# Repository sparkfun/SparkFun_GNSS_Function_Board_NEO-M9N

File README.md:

SparkFun MicroMod GNSS Function Board - NEO-M9N
========================================

[*SparkFun MicroMod GNSS Function Board - NEO-M9N (GPS-18378)*](https://www.sparkfun.com/products/18378)

The SparkFun NEO-M9N GNSS Function Board is a high quality, geospatial board with equally impressive configuration options. The NEO-M9N module that is populated on this board is a 92-channel u-blox M9 engine GNSS receiver, meaning it can receive signals from the GPS, GLONASS, Galileo, and BeiDou constellations with ~1.5 meter accuracy. This Function Board supports concurrent reception of four GNSS. This maximizes position accuracy in challenging conditions, increasing precision and decreases lock time; and thanks to the on-board rechargeable battery, you'll have backup power enabling the GPS to get a hot lock within seconds!

Utilizing our handy M.2 MicroMod connector, no soldering is required to connect it to your system. Simply match up the key on your processor and function board's beveled edge connector to their respective key on the M.2 connector, then secure them to the Main Board with screws. Once connected, you'll have the option of choosing either the UART, SPI, or I<sup>2</sup>C (u-blox calls this Display Data Channel) port to communicate with the NEO-M9N.

The NEO-M9N module detects jamming and spoofing events and can reports them to the host, so that the system can react to such events. A SAW (Surface Acoustic Wave) filter combined with an LNA (Low Noise Amplifier) in the RF path is integrated into the NEO-M9N module which allows normal operation even under strong RF interferences.

U-blox based GPS products are configurable using the popular, but dense, Windows program called u-center. Plenty of different functions can be configured on the NEO-M9N: baud rates, update rates, geofencing, spoofing detection, external interrupts, SBAS/D-GPS, etc. All of this can be done within the [SparkFun Arduino Library](https://github.com/sparkfun/SparkFun_u-blox_GNSS_Arduino_Library) via the I<sup>2</sup>C bus!

The SparkFun GNSS Function Board - NEO-M9N includes a USB type C connector when configuring the module with u-center. Power is provided through the Function Board's edge pins and regulated down through the 3.3V voltage regulator. Two status LEDs are also included for 3V3 and PPS, which can be disabled by cutting the jumpers on the back of the board. A 1x3 header is populated on the board and includes a 2-pin selectable jumper when selecting the communication protocol between SPI or Serial/I<sup>2</sup>C. For advanced users, there are jumpers to disable the write protection for the EEPROM (WP), disconnecting the pull-up resistors (I2C), and placing the module in safe boot mode (SAFEBOOT). A U.FL connector is provided to connect a GNSS antenna of your choice to the module.  The board is equipped with an on-board rechargeable battery that provides power to the RTC on the NEO-M9N.  This reduces the time-to-first fix from a cold start (~24s) to a hot start (~2s). The battery will maintain RTC and GNSS orbit data without being connected to power for plenty of time. 

Repository Contents
-------------------

* **/Hardware** - Eagle design files (.brd, .sch)
* **/Production** - Production panel files (.brd)

Documentation
--------------

* **[Installing an Arduino Library Guide](https://learn.sparkfun.com/tutorials/installing-an-arduino-library/all)** - Basic information on how to install an Arduino library.
* **[Library](https://github.com/sparkfun/SparkFun_u-blox_GNSS_Arduino_Library)** - Arduino Library the SparkFun MicroMod GNSS Function Board - NEO-M9N.
* **[Hookup Guide](https://learn.sparkfun.com/tutorials/1999)** - Basic hookup guide for the SparkFun MicroMod GNSS Function Board - NEO-M9N.

Product Versions
----------------

* [GPS-18378](https://www.sparkfun.com/products/18378) - Initial release

Version History
---------------

* v1.2 - Initial Release

License Information
-------------------

This product is _**open source**_! 

Please review the LICENSE.md file for license information. 

If you have any questions or concerns on licensing, please contact technical support on our [SparkFun forums](https://forum.sparkfun.com/viewforum.php?f=152).

Distributed as-is; no warranty is given.

- Your friends at SparkFun.

_<COLLABORATION CREDIT>_

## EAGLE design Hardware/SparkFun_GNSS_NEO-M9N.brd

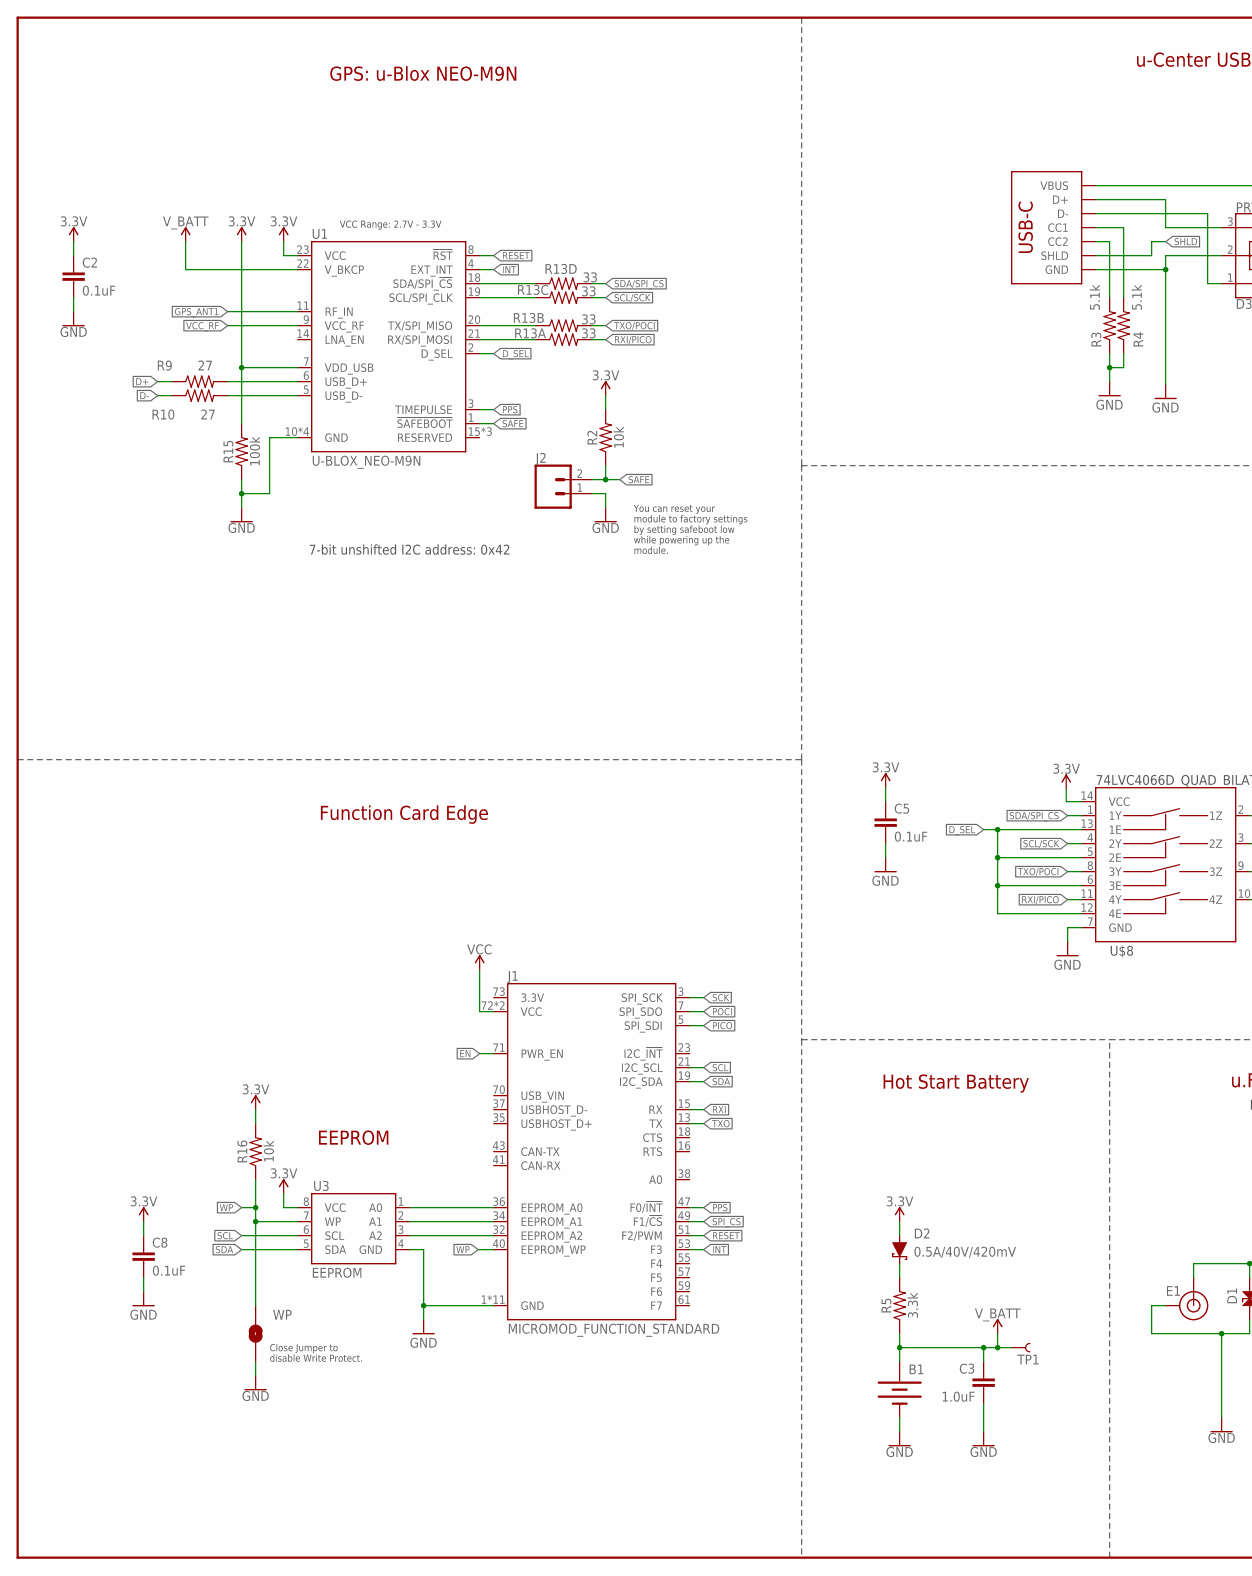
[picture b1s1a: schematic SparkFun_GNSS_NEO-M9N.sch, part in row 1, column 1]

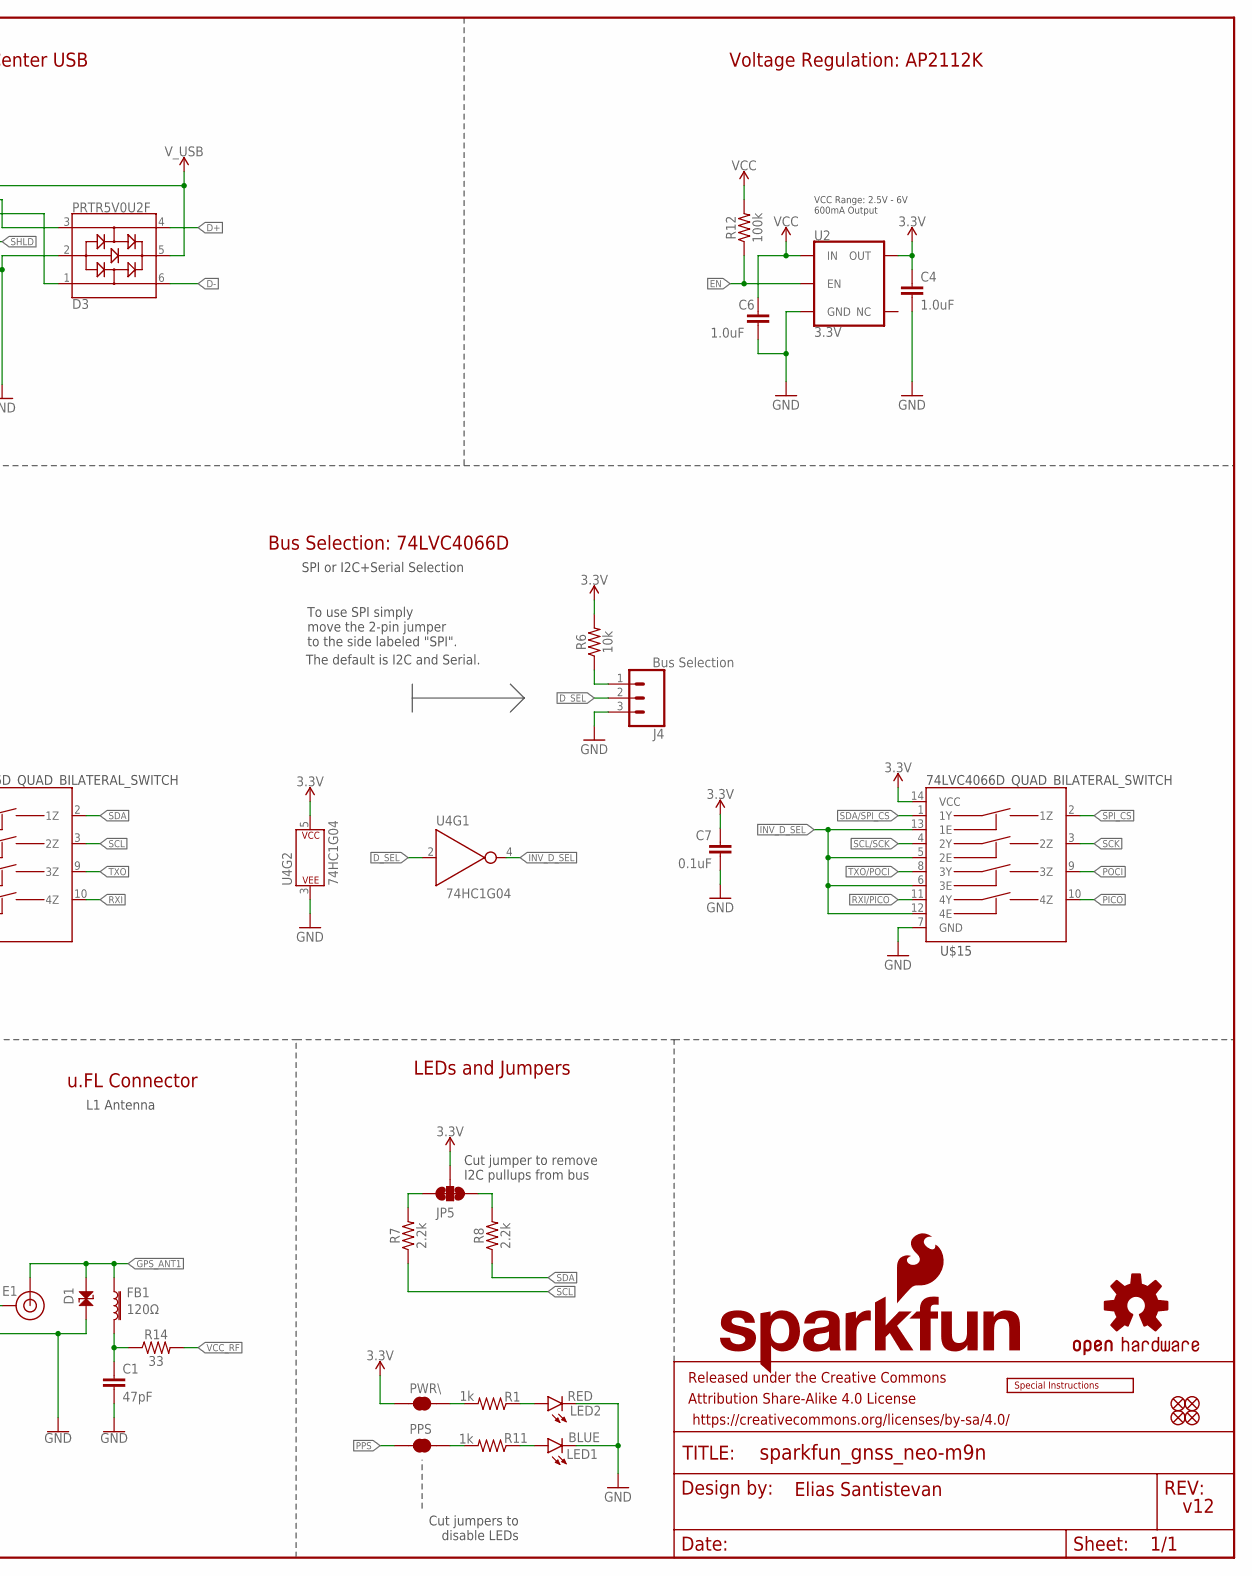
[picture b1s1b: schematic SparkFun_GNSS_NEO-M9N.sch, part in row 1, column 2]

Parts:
B1: 6.8MM_COIN_CELL; MS421R_IV03E
C1: 47pF; 0402
C2: 0.1uF; 0402-TIGHT
C3, C4, C6: 1.0uF; 0603
C5, C7, C8: 0.1uF; 0603
D1: PESD0402-0402T; 0402-TIGHT
D2: 0.5A/40V/420mV; SOD-323
D3: PRTR5V0U2F; SOT886
E1: U.FL
FB1: 120Ω; 0402
FD1, FD2, FD3, FD4: FIDUCIAL1X2; FIDUCIAL-1X2
FRAME2: FRAME-LEDGER; CREATIVE_COMMONS
J1: MICROMOD_FUNCTION_STANDARD; M.2-CARD-E-22_FUNCTION_STANDARD
J2: CONN_02; 1X02
J3: USB_C_2-LAYER_PADS; USB-C-16P-2LAYER-PADS
J4: Bus Selection; 1X03_LOCK
JP5: JUMPER-SMT_3_2-NC_TRACE_SILK; SMT-JUMPER_3_2-NC_TRACE_SILK
LED1: BLUE; LED-0603
LED2: RED; LED-0603
LOGO1: SPECIAL_INSTRUCTIONS-ORDERING; ORDERING_INSTRUCTIONS
LOGO2: SFE_LOGO_NAME_FLAME.2_INCH; SFE_LOGO_NAME_FLAME_.2
LOGO3: OSHW-LOGOS; OSHW-LOGO-S
PPS: JUMPER-SMT_2_NC_TRACE_SILK; SMT-JUMPER_2_NC_TRACE_SILK
PWR\: JUMPER-SMT_2_NC_TRACE_SILK; SMT-JUMPER_2_NC_TRACE_SILK
R1, R11: 1k; 0603
R2, R6, R16: 10k; 0603
R3, R4: 5.1k; 0603
R5: 3.3k; 0603
R7, R8: 2.2k; 0603
R9, R10: 27; 0603
R12, R15: 100k; 0603
R13: 33; 1206_RA
R14: 33; 0402
TP1: TEST-POINT3X4; PAD.03X.04
U1: U-BLOX_NEO-M9N; NEO-M9N/M8T/M8U/D9S
U2: 3.3V; SOT23-5
U3: EEPROM; SO08
U4: 74HC1G04; SOT353
U$8, U$15: 74LVC4066D_QUAD_BILATERAL_SWITCH; SO14
WP: JUMPER-SMT_2_NO_SILK; SMT-JUMPER_2_NO_SILK

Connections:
3.3V: C2.1, C4.1, C5.1, C7.1, C8.1, D2.A, JP5.2, PWR\.2, R2.2, R6.2, R15.2, R16.2, U1.7 (VDD_USB), U1.23 (VCC), U2.5 (OUT), U3.8 (VCC), U4.5 (P$V+), U$8.14 (VCC), U$15.14 (VCC)
!RESET: J1.51 (F2/PWM), U1.8 (!RST)
!SAFE: J2.2, R2.1, U1.1 (!SAFEBOOT!)
A0: J1.36 (EEPROM_A0), U3.1 (A0)
A1: J1.34 (EEPROM_A1), U3.2 (A1)
A2: J1.32 (EEPROM_A2), U3.3 (A2)
D+: D3.4, R9.1
D-: D3.6, R10.1
D_SEL: J4.2, U1.2 (D_SEL), U4.2 (A), U$8.5 (2E), U$8.6 (3E), U$8.12 (4E), U$8.13 (1E)
EN: J1.71 (PWR_EN), R12.1, U2.3 (EN)
GND: B1.-, C1.2, C2.2, C3.2, C4.2, C5.2, C6.2, C7.2, C8.2, D1.1, D3.2, E1.1 (GND), E1.2 (GND), J1.1 (GND), J1.33 (GND), J1.39 (GND), J1.45 (GND), J1.75 (GND), J1.GND1 (GND), J1.GND2 (GND), J1.GND3 (GND), J1.GND4 (GND), J1.GND5 (GND), J1.GND6 (GND), J2.1, J3.GND, J3.GND2 (GND), J4.3, LED1.C, LED2.C, R3.1, R4.1, R15.1, U1.10 (GND), U1.12 (GND), U1.13 (GND), U1.24 (GND), U2.2 (GND), U3.4 (GND), U4.3 (P$V-), U$8.7 (GND), U$15.7 (GND), WP.1
GPS_ANT1: D1.2, E1.FEED (SIGNAL), FB1.1, U1.11 (RF_IN)
INT: J1.53 (F3), U1.4 (EXT_INT)
INV_D_SEL: U4.4 (Y), U$15.5 (2E), U$15.6 (3E), U$15.12 (4E), U$15.13 (1E)
unnamed: PWR\.1, R1.2
unnamed: LED1.A, R11.1
unnamed: C1.1, FB1.2, R14.1
unnamed: PPS.1, R11.2
unnamed: JP5.1, R8.2
unnamed: D2.C, R5.2
unnamed: J3.A5 (CC1), R4.2
unnamed: JP5.3, R7.2
unnamed: J3.B5 (CC2), R3.2
unnamed: LED2.A, R1.1
unnamed: R9.2, U1.6 (USB_D+)
unnamed: R10.2, U1.5 (USB_D-)
unnamed: J4.1, R6.1
PICO: J1.5 (SPI_SDI), U$15.10 (4Z)
POCI: J1.7 (SPI_SDO), U$15.9 (3Z)
PPS: J1.47 (F0/!INT!), PPS.2, U1.3 (TIMEPULSE)
RXI: J1.15 (RX), U$8.10 (4Z)
RXI/PICO: R13.P8 (2), U$8.11 (4Y), U$15.11 (4Y)
RXLV: R13.P1 (1), U1.21 (RX/SPI_MOSI)
SCK: J1.3 (SPI_SCK), U$15.3 (2Z)
SCL: J1.21 (I2C_SCL), R7.1, U3.6 (SCL), U$8.3 (2Z)
SCL/SCK: R13.P6 (2), U$8.4 (2Y), U$15.4 (2Y)
SCL_LV: R13.P3 (1), U1.19 (SCL/SPI_CLK)
SDA: J1.19 (I2C_SDA), R8.1, U3.5 (SDA), U$8.2 (1Z)
SDA/SPI_!CS!: R13.P5 (2), U$8.1 (1Y), U$15.1 (1Y)
SDA_LV: R13.P4 (1), U1.18 (SDA/SPI_!CS!)
SHLD: J3.SHLD1 (SHLD), J3.SHLD2 (SHLD), J3.SHLD3 (SHLD), J3.SHLD4 (SHLD)
SPI_!CS!: J1.49 (F1/!CS!), U$15.2 (1Z)
TXLV: R13.P2 (1), U1.20 (TX/SPI_MISO)
TXO: J1.13 (TX), U$8.9 (3Z)
TXO/POCI: R13.P7 (2), U$8.8 (3Y), U$15.8 (3Y)
USB_D+: D3.3, J3.A6 (D+), J3.B6 (D+)
USB_D-: D3.1, J3.A7 (D-), J3.B7 (D-)
VCC: C6.1, J1.72 (VCC), J1.74 (VCC), R12.2, U2.1 (IN)
VCC_RF: R14.2, U1.9 (VCC_RF)
V_BATT: B1.+, C3.1, R5.1, TP1.1, U1.22 (V_BKCP)
V_USB: D3.5, J3.VBUS1 (VBUS), J3.VBUS2 (VBUS)
WP: J1.40 (EEPROM_WP), R16.1, U3.7 (WP), WP.2

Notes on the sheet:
v12
7-bit unshifted I2C address: 0x42
Cut jumper to remove I2C pullups from bus
Cut jumpers to disable LEDs
Elias Santistevan
LEDs and Jumpers
Hot Start Battery
GPS: u-Blox NEO-M9N
u.FL Connector
VCC Range: 2.7V - 3.3V
VCC Range: 2.5V - 6V 600mA Output
u-Center USB
Function Card Edge
EEPROM
Voltage Regulation: AP2112K
L1 Antenna
Bus Selection: 74LVC4066D
To use SPI simply move the 2-pin jumper to the side labeled "SPI".
SPI or I2C+Serial Selection
The default is I2C and Serial.
Close Jumper to disable Write Protect.
You can reset your module to factory settings by setting safeboot low while powering up the module.

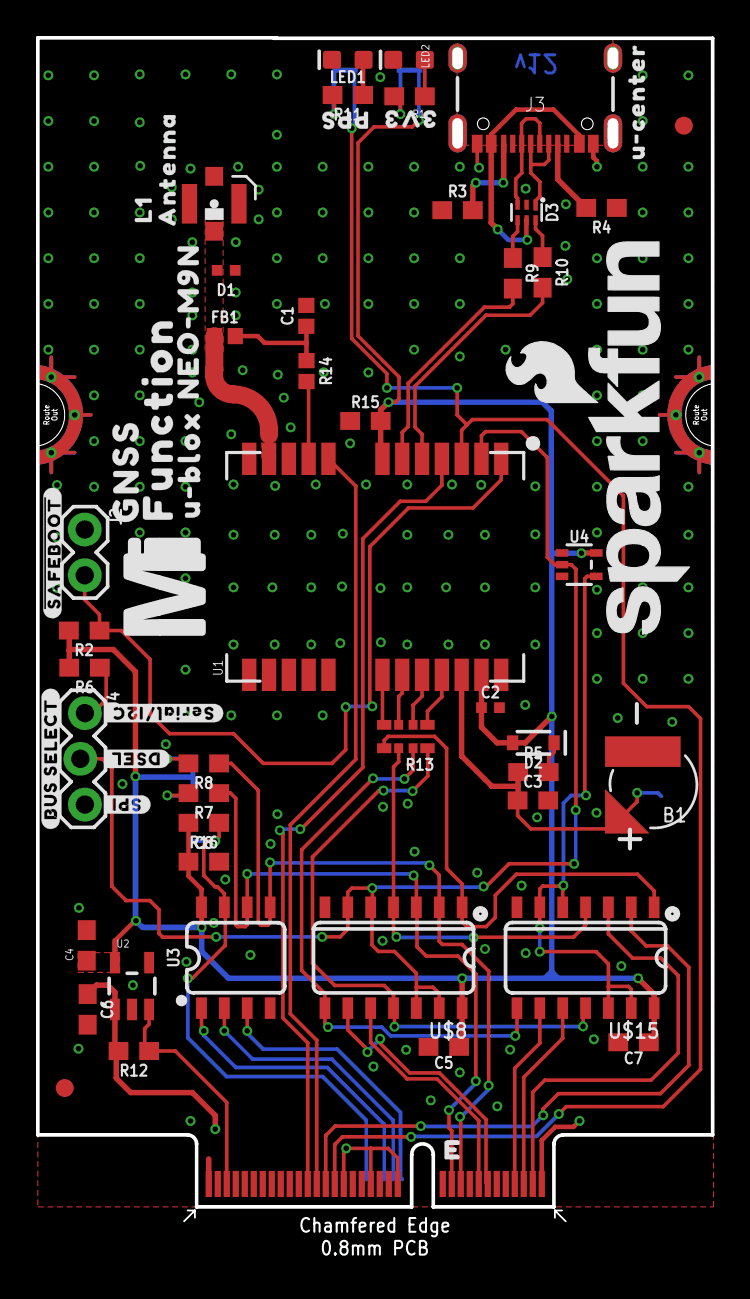
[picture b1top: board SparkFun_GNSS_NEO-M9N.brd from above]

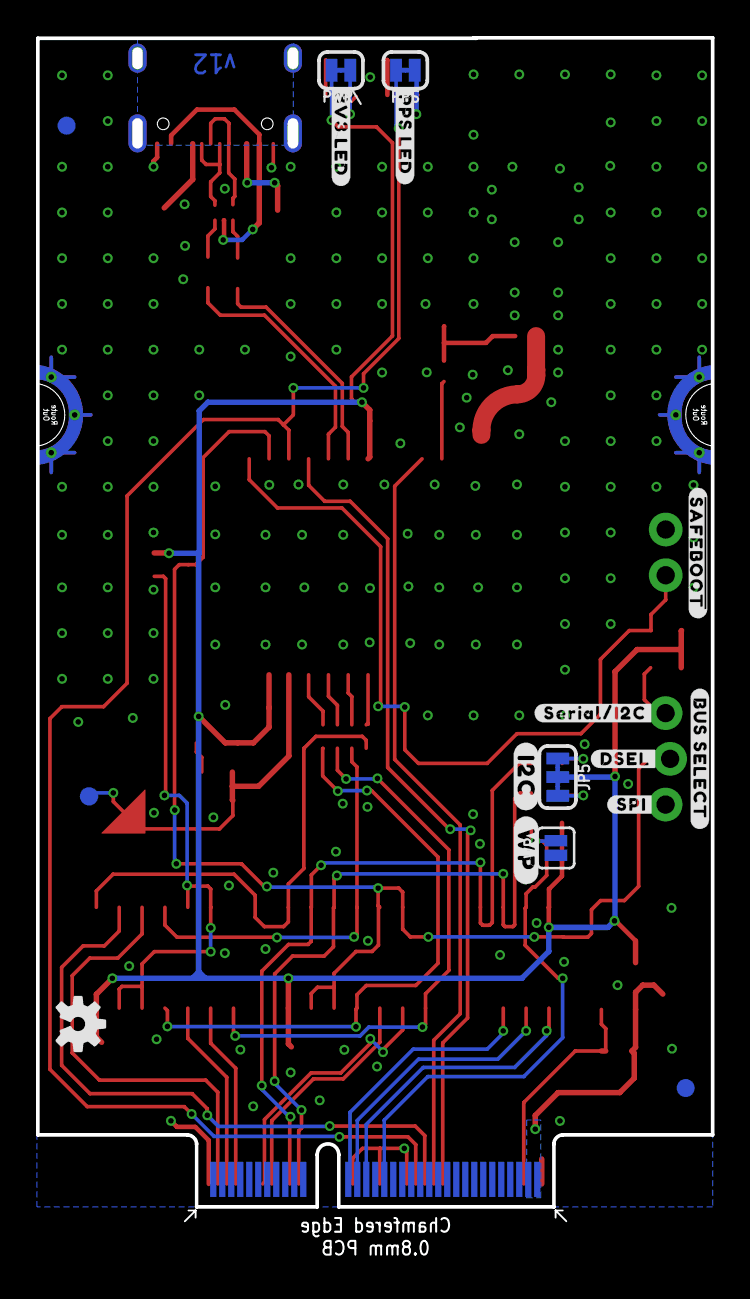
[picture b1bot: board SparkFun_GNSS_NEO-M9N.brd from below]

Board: 2 copper layers, 37.1 x 67.6 mm, 79 parts (17 on the bottom side), 52 nets.

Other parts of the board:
U$1: 3V313
U$2: PPS13
U$3: FUNCTION521
U$4, U$23: ##SAFEBOOT##882188213
U$5: U#BLOX11
U$6: NEO#M9N12
U$7: ANTENNA14
U$9: U#CENTER15
U$10: #I2C#18
U$11: MICROMOD_MI_LOGO_1
U$12: #3V3_LED#403132222514
U$13: #PPS_LED#403132222514
U$14: L1321542
U$16, U$24: #SPI#40313521
U$17, U$26: #SERIAL#I2C#40313523
U$18, U$22: #BUS_SELECT#509
U$19, U$25: #DSEL#40313522
U$20: #WP#13215403132222564
U$21: GNSS2222502

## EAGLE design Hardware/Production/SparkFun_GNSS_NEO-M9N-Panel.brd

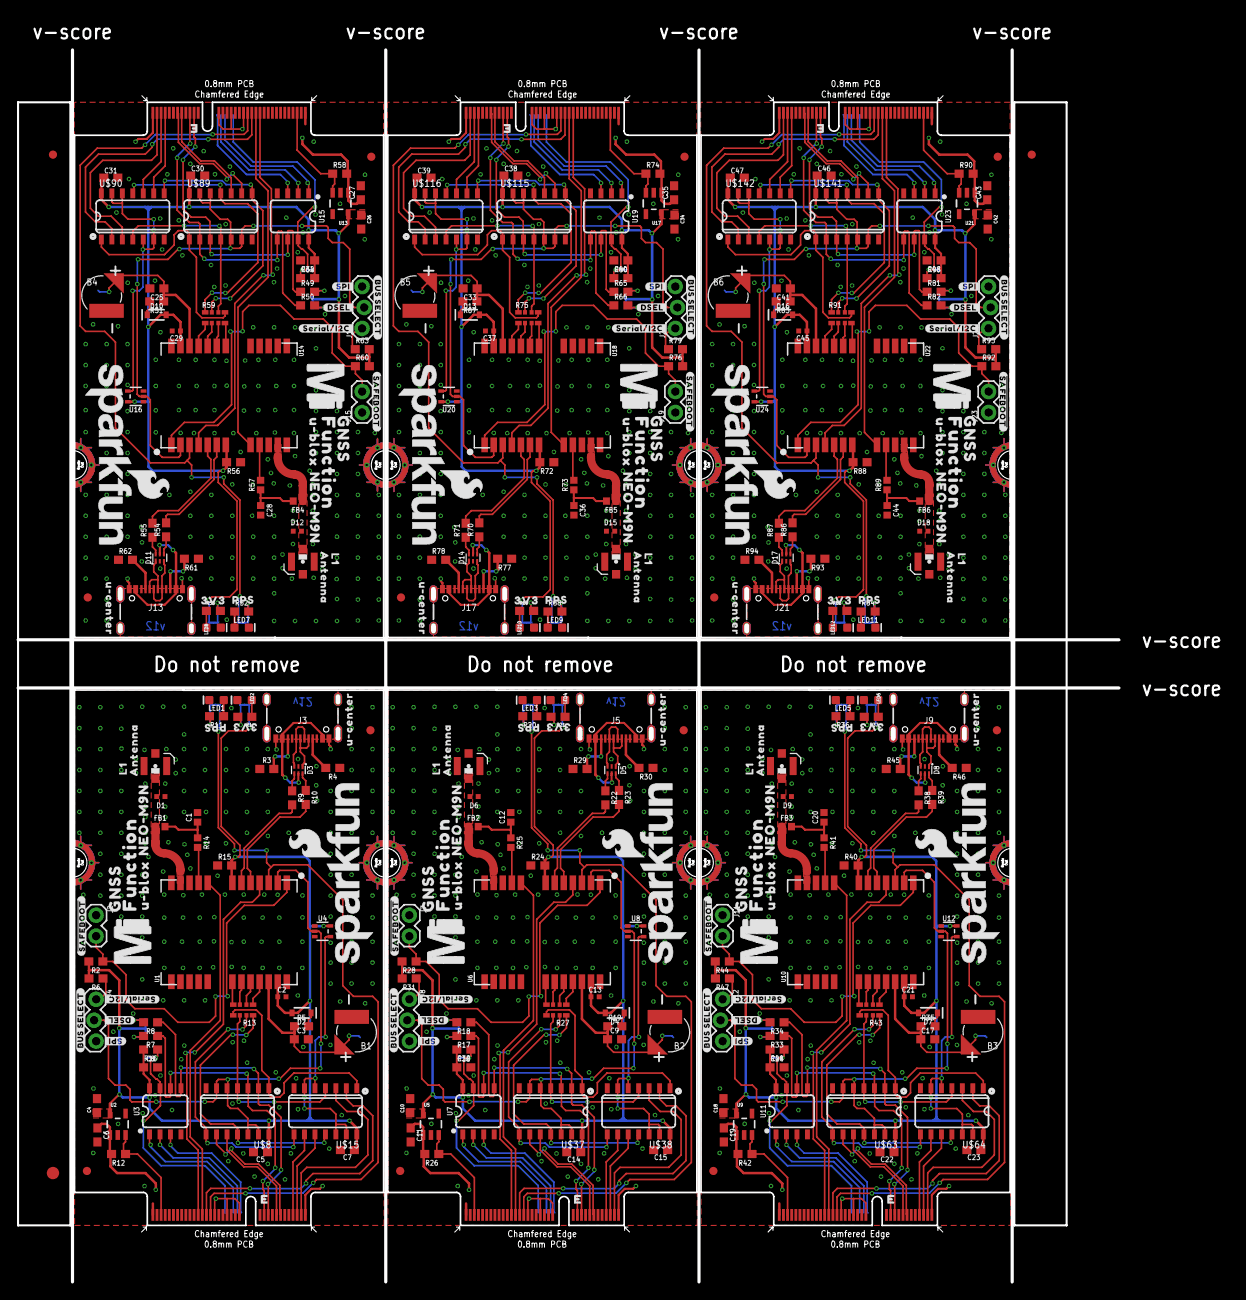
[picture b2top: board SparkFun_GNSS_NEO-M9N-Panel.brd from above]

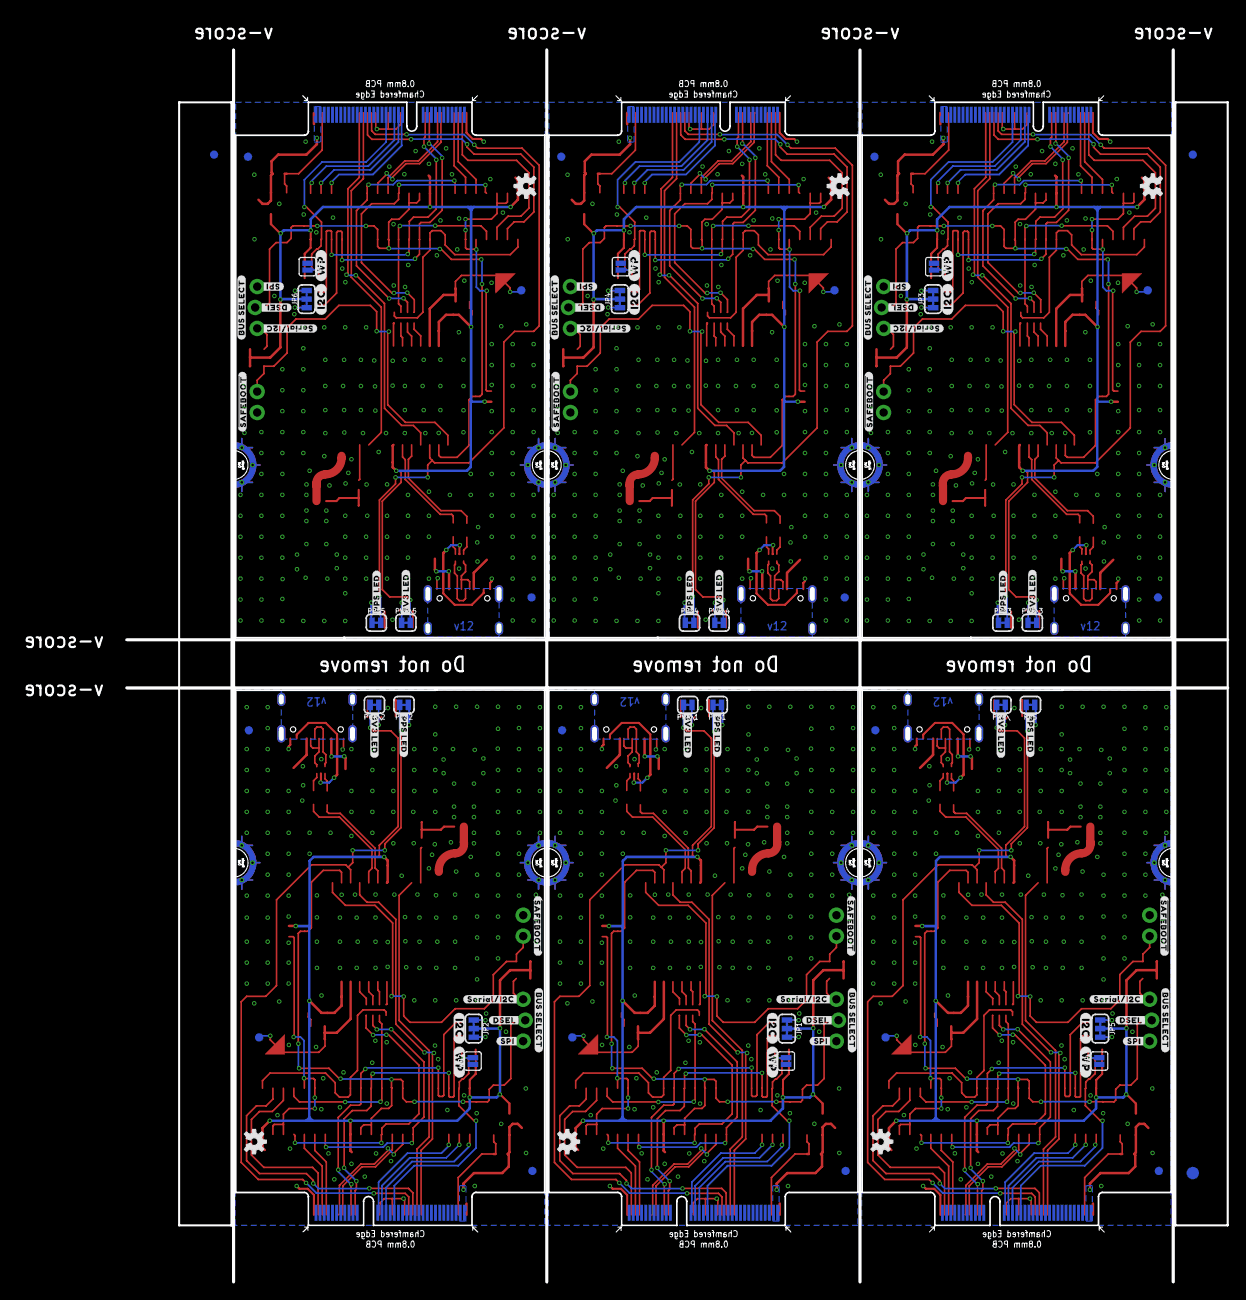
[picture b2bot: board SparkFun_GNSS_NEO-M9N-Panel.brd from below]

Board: 2 copper layers, 146.5 x 153.1 mm, 468 parts (105 on the bottom side), 312 nets.

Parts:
B1, B2, B3, B4, B5, B6: 6.8MM_COIN_CELL; MS421R_IV03E
C1, C12, C20, C28, C36, C44: 47pF; 0402
C2, C13, C21, C29, C37, C45: 0.1uF; 0402-TIGHT
C3, C4, C6, C9, C10, C11, C17, C18, C19, C25, C26, C27, C33, C34, C35, C41, C42, C43: 1.0uF; 0603
C5, C7, C8, C14, C15, C16, C22, C23, C24, C30, C31, C32, C38, C39, C40, C46, C47, C48: 0.1uF; 0603
D1, D6, D9, D12, D15, D18: PESD0402-0402T; 0402-TIGHT
D2, D4, D7, D10, D13, D16: 0.5A/40V/420mV; SOD-323
D3, D5, D8, D11, D14, D17: PRTR5V0U2F; SOT886
E1, E2, E3, E4, E5, E6: U.FL
E$1, E$2, E$3, E$4: FIDUCIAL-1X2
E$5, E$6: FIDUCIAL-1.5X3
FB1, FB2, FB3, FB4, FB5, FB6: 120Ω; 0402
FD1, FD2, FD3, FD4, FD5, FD6, FD7, FD8, FD9, FD10, FD11, FD12, FD13, FD14, FD15, FD16, FD17, FD18, FD19, FD20, FD21, FD22, FD23, FD24: FIDUCIAL1X2; FIDUCIAL-1X2
J1, J6, J10, J14, J18, J22: MICROMOD_FUNCTION_STANDARD; M.2-CARD-E-22_FUNCTION_STANDARD
J2, J7, J11, J15, J19, J23: 1X02
J3, J5, J9, J13, J17, J21: USB-C-16P-2LAYER-PADS
J4, J8, J12, J16, J20, J24: Bus Selection; 1X03_LOCK
JP1, JP2, JP3, JP4, JP5, JP6: JUMPER-SMT_3_2-NC_TRACE_SILK; SMT-JUMPER_3_2-NC_TRACE_SILK
LED1, LED3, LED5, LED7, LED9, LED11: BLUE; LED-0603
LED2, LED4, LED6, LED8, LED10, LED12: RED; LED-0603
LOGO1, LOGO2, LOGO5, LOGO7, LOGO9, LOGO11: SFE_LOGO_NAME_FLAME.2_INCH; SFE_LOGO_NAME_FLAME_.2
LOGO3, LOGO4, LOGO6, LOGO8, LOGO10, LOGO12: OSHW-LOGOS; OSHW-LOGO-S
PPS, PPS1, PPS2, PPS3, PPS4, PPS5: JUMPER-SMT_2_NC_TRACE_SILK; SMT-JUMPER_2_NC_TRACE_SILK
PWR\, PWR\1, PWR\2, PWR\3, PWR\4, PWR\5: JUMPER-SMT_2_NC_TRACE_SILK; SMT-JUMPER_2_NC_TRACE_SILK
R1, R11, R20, R21, R36, R37, R52, R53, R68, R69, R84, R85: 1k; 0603
R2, R6, R16, R28, R31, R32, R44, R47, R48, R60, R63, R64, R76, R79, R80, R92, R95, R96: 10k; 0603
R3, R4, R29, R30, R45, R46, R61, R62, R77, R78, R93, R94: 5.1k; 0603
R5, R19, R35, R51, R67, R83: 3.3k; 0603
R7, R8, R17, R18, R33, R34, R49, R50, R65, R66, R81, R82: 2.2k; 0603
R9, R10, R22, R23, R38, R39, R54, R55, R70, R71, R86, R87: 27; 0603
R12, R15, R24, R26, R40, R42, R56, R58, R72, R74, R88, R90: 100k; 0603
R13, R27, R43, R59, R75, R91: 33; 1206_RA
R14, R25, R41, R57, R73, R89: 33; 0402
TP1, TP2, TP3, TP4, TP5, TP6: TEST-POINT3X4; PAD.03X.04
U1, U6, U10, U14, U18, U22: U-BLOX_NEO-M9N; NEO-M9N/M8T/M8U/D9S
U2, U5, U9, U13, U17, U21: 3.3V; SOT23-5
U3, U7, U11, U15, U19, U23: EEPROM; SO08
U4, U8, U12, U16, U20, U24: 74HC1G04; SOT353
U$1, U$27, U$53, U$79, U$105, U$131: 3V313
U$2, U$28, U$54, U$80, U$106, U$132: PPS13
U$3, U$34, U$60, U$86, U$112, U$138: FUNCTION521
U$4, U$23, U$48, U$49, U$74, U$75, U$100, U$101, U$126, U$127, U$152, U$153: ##SAFEBOOT##882188213
U$5, U$29, U$55, U$81, U$107, U$133: U#BLOX11
U$6, U$30, U$56, U$82, U$108, U$134: NEO#M9N12
U$7, U$31, U$57, U$83, U$109, U$135: ANTENNA14
U$8, U$15, U$37, U$38, U$63, U$64, U$89, U$90, U$115, U$116, U$141, U$142: 74LVC4066D_QUAD_BILATERAL_SWITCH; SO14
U$9, U$32, U$58, U$84, U$110, U$136: U#CENTER15
U$10, U$33, U$59, U$85, U$111, U$137: #I2C#18
U$11, U$35, U$61, U$87, U$113, U$139: MICROMOD_MI_LOGO_1
U$12, U$45, U$71, U$97, U$123, U$149: #3V3_LED#403132222514
U$13, U$46, U$72, U$98, U$124, U$150: #PPS_LED#403132222514
U$14, U$36, U$62, U$88, U$114, U$140: L1321542
U$16, U$24, U$41, U$50, U$67, U$76, U$93, U$102, U$119, U$128, U$145, U$154: #SPI#40313521
U$17, U$26, U$42, U$52, U$68, U$78, U$94, U$104, U$120, U$130, U$146, U$156: #SERIAL#I2C#40313523
U$18, U$22, U$39, U$47, U$65, U$73, U$91, U$99, U$117, U$125, U$143, U$151: #BUS_SELECT#509
U$19, U$25, U$40, U$51, U$66, U$77, U$92, U$103, U$118, U$129, U$144, U$155: #DSEL#40313522
U$20, U$43, U$69, U$95, U$121, U$147: #WP#13215403132222564
U$21, U$44, U$70, U$96, U$122, U$148: GNSS2222502
WP, WP1, WP2, WP3, WP4, WP5: JUMPER-SMT_2_NO_SILK; SMT-JUMPER_2_NO_SILK

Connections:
3.3V: C2.1, C4.1, C5.1, C7.1, C8.1, D2.A, JP5.2, PWR\.2, R2.2, R6.2, R15.2, R16.2, U1.7, U1.23, U2.5, U3.8, U4.5, U$8.14, U$15.14
3.3V1: C10.1, C13.1, C14.1, C15.1, C16.1, D4.A, JP1.2, PWR\1.2, R24.2, R28.2, R31.2, R32.2, U5.5, U6.7, U6.23, U7.8, U8.5, U$37.14, U$38.14
3.3V2: C18.1, C21.1, C22.1, C23.1, C24.1, D7.A, JP2.2, PWR\2.2, R40.2, R44.2, R47.2, R48.2, U9.5, U10.7, U10.23, U11.8, U12.5, U$63.14, U$64.14
3.3V3: C26.1, C29.1, C30.1, C31.1, C32.1, D10.A, JP3.2, PWR\3.2, R56.2, R60.2, R63.2, R64.2, U13.5, U14.7, U14.23, U15.8, U16.5, U$89.14, U$90.14
3.3V4: C34.1, C37.1, C38.1, C39.1, C40.1, D13.A, JP4.2, PWR\4.2, R72.2, R76.2, R79.2, R80.2, U17.5, U18.7, U18.23, U19.8, U20.5, U$115.14, U$116.14
3.3V5: C42.1, C45.1, C46.1, C47.1, C48.1, D16.A, JP6.2, PWR\5.2, R88.2, R92.2, R95.2, R96.2, U21.5, U22.7, U22.23, U23.8, U24.5, U$141.14, U$142.14
!RESET: J1.51, U1.8
!RESET1: J6.51, U6.8
!RESET2: J10.51, U10.8
!RESET3: J14.51, U14.8
!RESET4: J18.51, U18.8
!RESET5: J22.51, U22.8
!SAFE: J2.2, R2.1, U1.1
!SAFE1: J7.2, R28.1, U6.1
!SAFE2: J11.2, R44.1, U10.1
!SAFE3: J15.2, R60.1, U14.1
!SAFE4: J19.2, R76.1, U18.1
!SAFE5: J23.2, R92.1, U22.1
A0: J1.36, U3.1
A1: J1.34, U3.2
A2: J1.32, U3.3
A3: J6.36, U7.1
A4: J6.32, U7.3
A5: J6.34, U7.2
A6: J10.36, U11.1
A7: J10.32, U11.3
A8: J10.34, U11.2
A9: J14.36, U15.1
A10: J14.32, U15.3
A11: J14.34, U15.2
A12: J18.36, U19.1
A13: J18.32, U19.3
A14: J18.34, U19.2
A15: J22.36, U23.1
A16: J22.32, U23.3
A17: J22.34, U23.2
D+: D3.4, R9.1
D+1: D5.4, R22.1
D+2: D8.4, R38.1
D+3: D11.4, R54.1
D+4: D14.4, R70.1
D+5: D17.4, R86.1
D-: D3.6, R10.1
D-1: D5.6, R23.1
D-2: D8.6, R39.1
D-3: D11.6, R55.1
D-4: D14.6, R71.1
D-5: D17.6, R87.1
D_SEL: J4.2, U1.2, U4.2, U$8.5, U$8.6, U$8.12, U$8.13
D_SEL1: J8.2, U6.2, U8.2, U$37.5, U$37.6, U$37.12, U$37.13
D_SEL2: J12.2, U10.2, U12.2, U$63.5, U$63.6, U$63.12, U$63.13
D_SEL3: J16.2, U14.2, U16.2, U$89.5, U$89.6, U$89.12, U$89.13
D_SEL4: J20.2, U18.2, U20.2, U$115.5, U$115.6, U$115.12, U$115.13
D_SEL5: J24.2, U22.2, U24.2, U$141.5, U$141.6, U$141.12, U$141.13
EN: J1.71, R12.1, U2.3
EN1: J6.71, R26.1, U5.3
EN2: J10.71, R42.1, U9.3
EN3: J14.71, R58.1, U13.3
EN4: J18.71, R74.1, U17.3
EN5: J22.71, R90.1, U21.3
GND: B1.-, C1.2, C2.2, C3.2, C4.2, C5.2, C6.2, C7.2, C8.2, D1.1, D3.2, E1.1, E1.2, J1.1, J1.33, J1.39, J1.45, J1.75, J1.GND1, J1.GND2, J1.GND3, J1.GND4, J1.GND5, J1.GND6, J2.1, J3.GND, J3.GND2, J4.3, LED1.C, LED2.C, R3.1, R4.1, R15.1, U1.10, U1.12, U1.13, U1.24, U2.2, U3.4, U4.3, U$8.7, U$15.7, WP.1
GND1: B2.-, C9.2, C10.2, C11.2, C12.2, C13.2, C14.2, C15.2, C16.2, D5.2, D6.1, E2.1, E2.2, J5.GND, J5.GND2, J6.1, J6.33, J6.39, J6.45, J6.75, J6.GND1, J6.GND2, J6.GND3, J6.GND4, J6.GND5, J6.GND6, J7.1, J8.3, LED3.C, LED4.C, R24.1, R29.1, R30.1, U5.2, U6.10, U6.12, U6.13, U6.24, U7.4, U8.3, U$37.7, U$38.7, WP1.1
GND2: B3.-, C17.2, C18.2, C19.2, C20.2, C21.2, C22.2, C23.2, C24.2, D8.2, D9.1, E3.1, E3.2, J9.GND, J9.GND2, J10.1, J10.33, J10.39, J10.45, J10.75, J10.GND1, J10.GND2, J10.GND3, J10.GND4, J10.GND5, J10.GND6, J11.1, J12.3, LED5.C, LED6.C, R40.1, R45.1, R46.1, U9.2, U10.10, U10.12, U10.13, U10.24, U11.4, U12.3, U$63.7, U$64.7, WP2.1
GND3: B4.-, C25.2, C26.2, C27.2, C28.2, C29.2, C30.2, C31.2, C32.2, D11.2, D12.1, E4.1, E4.2, J13.GND, J13.GND2, J14.1, J14.33, J14.39, J14.45, J14.75, J14.GND1, J14.GND2, J14.GND3, J14.GND4, J14.GND5, J14.GND6, J15.1, J16.3, LED7.C, LED8.C, R56.1, R61.1, R62.1, U13.2, U14.10, U14.12, U14.13, U14.24, U15.4, U16.3, U$89.7, U$90.7, WP3.1
GND4: B5.-, C33.2, C34.2, C35.2, C36.2, C37.2, C38.2, C39.2, C40.2, D14.2, D15.1, E5.1, E5.2, J17.GND, J17.GND2, J18.1, J18.33, J18.39, J18.45, J18.75, J18.GND1, J18.GND2, J18.GND3, J18.GND4, J18.GND5, J18.GND6, J19.1, J20.3, LED9.C, LED10.C, R72.1, R77.1, R78.1, U17.2, U18.10, U18.12, U18.13, U18.24, U19.4, U20.3, U$115.7, U$116.7, WP4.1
GND5: B6.-, C41.2, C42.2, C43.2, C44.2, C45.2, C46.2, C47.2, C48.2, D17.2, D18.1, E6.1, E6.2, J21.GND, J21.GND2, J22.1, J22.33, J22.39, J22.45, J22.75, J22.GND1, J22.GND2, J22.GND3, J22.GND4, J22.GND5, J22.GND6, J23.1, J24.3, LED11.C, LED12.C, R88.1, R93.1, R94.1, U21.2, U22.10, U22.12, U22.13, U22.24, U23.4, U24.3, U$141.7, U$142.7, WP5.1
GPS_ANT1: D1.2, E1.FEED, FB1.1, U1.11
GPS_ANT2: D6.2, E2.FEED, FB2.1, U6.11
GPS_ANT3: D9.2, E3.FEED, FB3.1, U10.11
GPS_ANT4: D12.2, E4.FEED, FB4.1, U14.11
GPS_ANT5: D15.2, E5.FEED, FB5.1, U18.11
GPS_ANT6: D18.2, E6.FEED, FB6.1, U22.11
INT: J1.53, U1.4
INT1: J6.53, U6.4
INT2: J10.53, U10.4
INT3: J14.53, U14.4
INT4: J18.53, U18.4
INT5: J22.53, U22.4
INV_D_SEL: U4.4, U$15.5, U$15.6, U$15.12, U$15.13
INV_D_SEL1: U8.4, U$38.5, U$38.6, U$38.12, U$38.13
INV_D_SEL2: U12.4, U$64.5, U$64.6, U$64.12, U$64.13
INV_D_SEL3: U16.4, U$90.5, U$90.6, U$90.12, U$90.13
INV_D_SEL4: U20.4, U$116.5, U$116.6, U$116.12, U$116.13
INV_D_SEL5: U24.4, U$142.5, U$142.6, U$142.12, U$142.13
unnamed: PWR\.1, R1.2
unnamed: LED1.A, R11.1
unnamed: C1.1, FB1.2, R14.1
unnamed: PPS.1, R11.2
unnamed: JP5.1, R8.2
unnamed: D2.C, R5.2
unnamed: J3.A5, R4.2
unnamed: JP5.3, R7.2
unnamed: J3.B5, R3.2
unnamed: LED2.A, R1.1
unnamed: R9.2, U1.6
unnamed: R10.2, U1.5
unnamed: J4.1, R6.1
unnamed: JP1.1, R18.2
unnamed: JP1.3, R17.2
unnamed: LED3.A, R20.1
unnamed: PPS1.1, R20.2
unnamed: D4.C, R19.2
unnamed: LED4.A, R21.1
unnamed: R22.2, U6.6
unnamed: R23.2, U6.5
unnamed: PWR\1.1, R21.2
unnamed: C12.1, FB2.2, R25.1
unnamed: J5.A5, R30.2
unnamed: J5.B5, R29.2
unnamed: J8.1, R31.1
unnamed: JP2.1, R34.2
unnamed: JP2.3, R33.2
unnamed: LED5.A, R36.1
unnamed: PPS2.1, R36.2
unnamed: D7.C, R35.2
unnamed: LED6.A, R37.1
unnamed: R38.2, U10.6
unnamed: R39.2, U10.5
unnamed: PWR\2.1, R37.2
unnamed: C20.1, FB3.2, R41.1
unnamed: J9.A5, R46.2
unnamed: J9.B5, R45.2
unnamed: J12.1, R47.1
unnamed: JP3.1, R50.2
unnamed: JP3.3, R49.2
unnamed: LED7.A, R52.1
unnamed: PPS3.1, R52.2
unnamed: D10.C, R51.2
unnamed: LED8.A, R53.1
unnamed: R54.2, U14.6
unnamed: R55.2, U14.5
unnamed: PWR\3.1, R53.2
unnamed: C28.1, FB4.2, R57.1
unnamed: J13.A5, R62.2
unnamed: J13.B5, R61.2
unnamed: J16.1, R63.1
unnamed: JP4.1, R66.2
unnamed: JP4.3, R65.2
unnamed: LED9.A, R68.1
unnamed: PPS4.1, R68.2
unnamed: D13.C, R67.2
unnamed: LED10.A, R69.1
unnamed: R70.2, U18.6
unnamed: R71.2, U18.5
unnamed: PWR\4.1, R69.2
unnamed: C36.1, FB5.2, R73.1
unnamed: J17.A5, R78.2
unnamed: J17.B5, R77.2
unnamed: J20.1, R79.1
unnamed: JP6.1, R82.2
unnamed: JP6.3, R81.2
unnamed: LED11.A, R84.1
unnamed: PPS5.1, R84.2
unnamed: D16.C, R83.2
unnamed: LED12.A, R85.1
unnamed: R86.2, U22.6
unnamed: R87.2, U22.5
unnamed: PWR\5.1, R85.2
unnamed: C44.1, FB6.2, R89.1
unnamed: J21.A5, R94.2
unnamed: J21.B5, R93.2
unnamed: J24.1, R95.1
PICO: J1.5, U$15.10
PICO1: J6.5, U$38.10
PICO2: J10.5, U$64.10
PICO3: J14.5, U$90.10
PICO4: J18.5, U$116.10
PICO5: J22.5, U$142.10
POCI: J1.7, U$15.9
POCI1: J6.7, U$38.9
POCI2: J10.7, U$64.9
POCI3: J14.7, U$90.9
POCI4: J18.7, U$116.9
POCI5: J22.7, U$142.9
PPS: J1.47, PPS.2, U1.3
PPS1: J6.47, PPS1.2, U6.3
PPS2: J10.47, PPS2.2, U10.3
PPS3: J14.47, PPS3.2, U14.3
PPS4: J18.47, PPS4.2, U18.3
PPS5: J22.47, PPS5.2, U22.3
RXI: J1.15, U$8.10
RXI1: J6.15, U$37.10
RXI2: J10.15, U$63.10
RXI3: J14.15, U$89.10
RXI4: J18.15, U$115.10
RXI5: J22.15, U$141.10
RXI/PICO: R13.P8, U$8.11, U$15.11
RXI/PICO1: R27.P8, U$37.11, U$38.11
RXI/PICO2: R43.P8, U$63.11, U$64.11
RXI/PICO3: R59.P8, U$89.11, U$90.11
RXI/PICO4: R75.P8, U$115.11, U$116.11
RXI/PICO5: R91.P8, U$141.11, U$142.11
RXLV: R13.P1, U1.21
RXLV1: R27.P1, U6.21
RXLV2: R43.P1, U10.21
RXLV3: R59.P1, U14.21
RXLV4: R75.P1, U18.21
RXLV5: R91.P1, U22.21
SCK: J1.3, U$15.3
SCK1: J6.3, U$38.3
SCK2: J10.3, U$64.3
SCK3: J14.3, U$90.3
SCK4: J18.3, U$116.3
SCK5: J22.3, U$142.3
SCL: J1.21, R7.1, U3.6, U$8.3
SCL1: J6.21, R17.1, U7.6, U$37.3
SCL2: J10.21, R33.1, U11.6, U$63.3
SCL3: J14.21, R49.1, U15.6, U$89.3
SCL4: J18.21, R65.1, U19.6, U$115.3
SCL5: J22.21, R81.1, U23.6, U$141.3
SCL/SCK: R13.P6, U$8.4, U$15.4
SCL/SCK1: R27.P6, U$37.4, U$38.4
SCL/SCK2: R43.P6, U$63.4, U$64.4
SCL/SCK3: R59.P6, U$89.4, U$90.4
SCL/SCK4: R75.P6, U$115.4, U$116.4
SCL/SCK5: R91.P6, U$141.4, U$142.4
SCL_LV: R13.P3, U1.19
SCL_LV1: R27.P3, U6.19
SCL_LV2: R43.P3, U10.19
SCL_LV3: R59.P3, U14.19
SCL_LV4: R75.P3, U18.19
SCL_LV5: R91.P3, U22.19
SDA: J1.19, R8.1, U3.5, U$8.2
SDA1: J6.19, R18.1, U7.5, U$37.2
SDA2: J10.19, R34.1, U11.5, U$63.2
SDA3: J14.19, R50.1, U15.5, U$89.2
SDA4: J18.19, R66.1, U19.5, U$115.2
SDA5: J22.19, R82.1, U23.5, U$141.2
SDA/SPI_!CS!: R13.P5, U$8.1, U$15.1
SDA/SPI_!CS!1: R27.P5, U$37.1, U$38.1
SDA/SPI_!CS!2: R43.P5, U$63.1, U$64.1
SDA/SPI_!CS!3: R59.P5, U$89.1, U$90.1
SDA/SPI_!CS!4: R75.P5, U$115.1, U$116.1
SDA/SPI_!CS!5: R91.P5, U$141.1, U$142.1
SDA_LV: R13.P4, U1.18
SDA_LV1: R27.P4, U6.18
SDA_LV2: R43.P4, U10.18
SDA_LV3: R59.P4, U14.18
SDA_LV4: R75.P4, U18.18
SDA_LV5: R91.P4, U22.18
SHLD: J3.SHLD1, J3.SHLD2, J3.SHLD3, J3.SHLD4
SHLD1: J5.SHLD1, J5.SHLD2, J5.SHLD3, J5.SHLD4
SHLD2: J9.SHLD1, J9.SHLD2, J9.SHLD3, J9.SHLD4
SHLD3: J13.SHLD1, J13.SHLD2, J13.SHLD3, J13.SHLD4
SHLD4: J17.SHLD1, J17.SHLD2, J17.SHLD3, J17.SHLD4
SHLD5: J21.SHLD1, J21.SHLD2, J21.SHLD3, J21.SHLD4
SPI_!CS!: J1.49, U$15.2
SPI_!CS!1: J6.49, U$38.2
SPI_!CS!2: J10.49, U$64.2
SPI_!CS!3: J14.49, U$90.2
SPI_!CS!4: J18.49, U$116.2
SPI_!CS!5: J22.49, U$142.2
TXLV: R13.P2, U1.20
TXLV1: R27.P2, U6.20
TXLV2: R43.P2, U10.20
TXLV3: R59.P2, U14.20
TXLV4: R75.P2, U18.20
TXLV5: R91.P2, U22.20
TXO: J1.13, U$8.9
TXO1: J6.13, U$37.9
TXO2: J10.13, U$63.9
TXO3: J14.13, U$89.9
TXO4: J18.13, U$115.9
TXO5: J22.13, U$141.9
TXO/POCI: R13.P7, U$8.8, U$15.8
TXO/POCI1: R27.P7, U$37.8, U$38.8
TXO/POCI2: R43.P7, U$63.8, U$64.8
TXO/POCI3: R59.P7, U$89.8, U$90.8
TXO/POCI4: R75.P7, U$115.8, U$116.8
TXO/POCI5: R91.P7, U$141.8, U$142.8
USB_D+: D3.3, J3.A6, J3.B6
USB_D+1: D5.3, J5.A6, J5.B6
USB_D+2: D8.3, J9.A6, J9.B6
USB_D+3: D11.3, J13.A6, J13.B6
USB_D+4: D14.3, J17.A6, J17.B6
USB_D+5: D17.3, J21.A6, J21.B6
USB_D-: D3.1, J3.A7, J3.B7
USB_D-1: D5.1, J5.A7, J5.B7
USB_D-2: D8.1, J9.A7, J9.B7
USB_D-3: D11.1, J13.A7, J13.B7
USB_D-4: D14.1, J17.A7, J17.B7
USB_D-5: D17.1, J21.A7, J21.B7
VCC: C6.1, J1.72, J1.74, R12.2, U2.1
VCC1: C11.1, J6.72, J6.74, R26.2, U5.1
VCC2: C19.1, J10.72, J10.74, R42.2, U9.1
VCC3: C27.1, J14.72, J14.74, R58.2, U13.1
VCC4: C35.1, J18.72, J18.74, R74.2, U17.1
VCC5: C43.1, J22.72, J22.74, R90.2, U21.1
VCC_RF: R14.2, U1.9
VCC_RF1: R25.2, U6.9
VCC_RF2: R41.2, U10.9
VCC_RF3: R57.2, U14.9
VCC_RF4: R73.2, U18.9
VCC_RF5: R89.2, U22.9
V_BATT: B1.+, C3.1, R5.1, TP1.1, U1.22
V_BATT1: B2.+, C9.1, R19.1, TP2.1, U6.22
V_BATT2: B3.+, C17.1, R35.1, TP3.1, U10.22
V_BATT3: B4.+, C25.1, R51.1, TP4.1, U14.22
V_BATT4: B5.+, C33.1, R67.1, TP5.1, U18.22
V_BATT5: B6.+, C41.1, R83.1, TP6.1, U22.22
V_USB: D3.5, J3.VBUS1, J3.VBUS2
V_USB1: D5.5, J5.VBUS1, J5.VBUS2
V_USB2: D8.5, J9.VBUS1, J9.VBUS2
V_USB3: D11.5, J13.VBUS1, J13.VBUS2
V_USB4: D14.5, J17.VBUS1, J17.VBUS2
V_USB5: D17.5, J21.VBUS1, J21.VBUS2
WP: J1.40, R16.1, U3.7, WP.2
WP1: J6.40, R32.1, U7.7, WP1.2
WP2: J10.40, R48.1, U11.7, WP2.2
WP3: J14.40, R64.1, U15.7, WP3.2
WP4: J18.40, R80.1, U19.7, WP4.2
WP5: J22.40, R96.1, U23.7, WP5.2

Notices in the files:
parts and their libraries:
SparkFun-Resistors: Licensing: Creative Commons ShareAlike 4.0 International - https://creativecommons.org/licenses/by-sa/4.0
SparkFun-Aesthetics: Released under the Creative Commons Attribution Share-Alike 4.0 License
SparkFun-Aesthetics: https://creativecommons.org/licenses/by-sa/4.0
